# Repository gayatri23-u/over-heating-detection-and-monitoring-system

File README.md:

# Over Heating Detection and Monitoring System

## Overview
This project is a PCB-based Over Heating Detection and Monitoring System developed to monitor temperature levels and detect overheating conditions in electronic systems.

The system continuously reads temperature data from sensors and provides alerts when the temperature exceeds a predefined threshold.

## Features
- Real-time temperature monitoring
- Overheating detection
- Alert/notification mechanism
- Custom PCB design
- Arduino-based implementation
- Compact and efficient system

## Technologies Used
- Arduino
- Embedded C/C++
- PCB Design
- Temperature Sensors

## Files Included
- Arduino source code
- PCB board design (.brd)
- Schematic files (.sch)

## Applications
- Industrial safety systems
- Electronic device monitoring
- Automation projects
- Temperature protection systems

## Author
Gayatri Pawar

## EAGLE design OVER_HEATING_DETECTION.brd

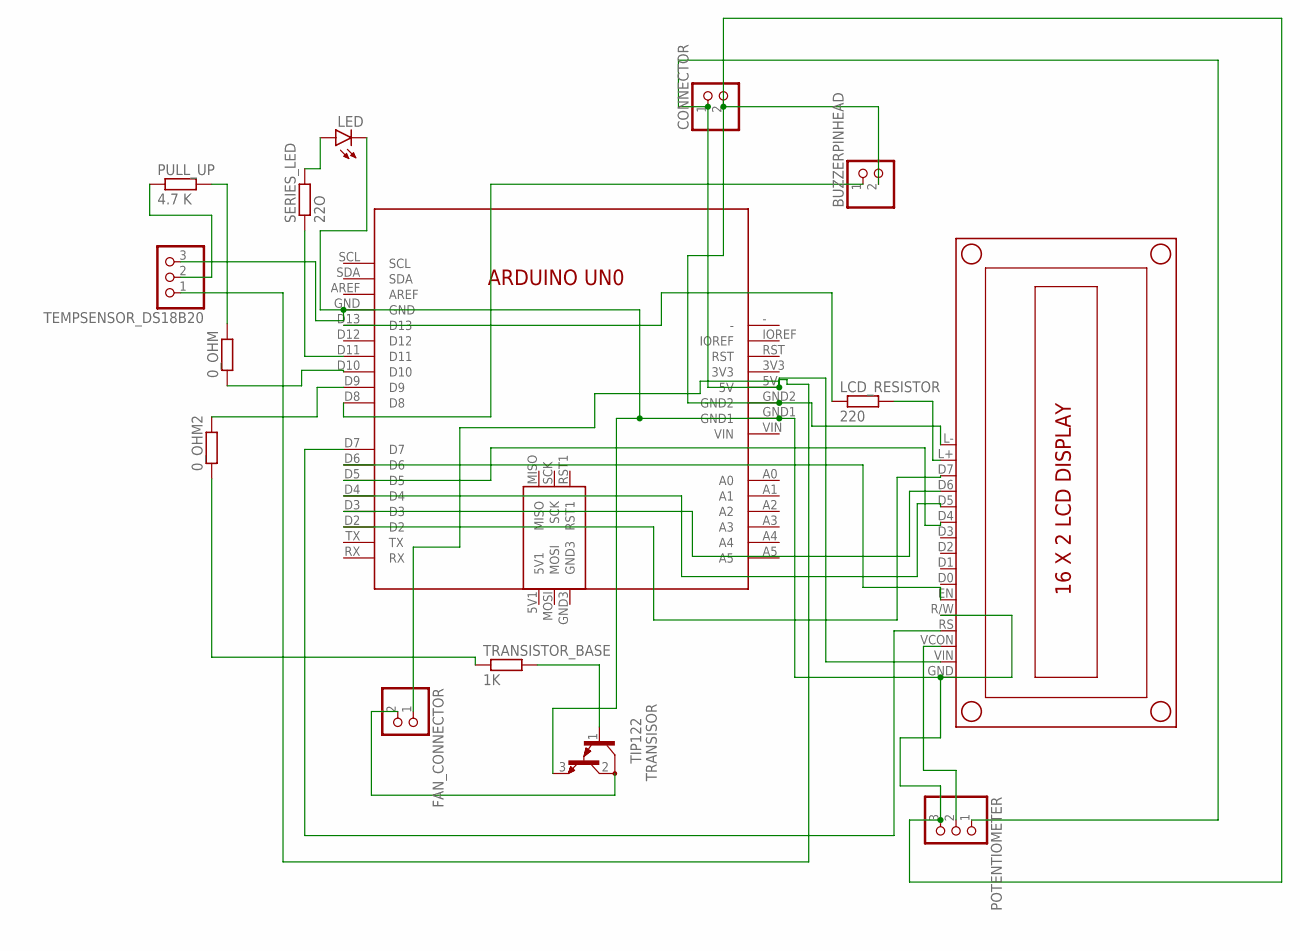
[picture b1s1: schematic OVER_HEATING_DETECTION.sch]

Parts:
0_OHM, 0_OHM2: R-EU_0204/7; 0204/7
BUZZERPINHEAD: PINHD-1X2; 1X02
CONNECTOR: PINHD-1X2; 1X02
FAN_CONNECTOR: PINHD-1X2; 1X02
LCD_RESISTOR: 220; 0204/7
LED: LED5MM
POTENTIOMETER: PINHD-1X3; 1X03
PULL_UP: 4.7 K; 0204/7
SERIES_LED: 22O; 0204/7
TEMPSENSOR_DS18B20: PINHD-1X3; 1X03
TRANSISOR: TIP122; TO220
TRANSISTOR_BASE: 1K; 0204/7
U$1: ARDUINO_UNO
U$2: 16X2_LCD_DISPLAY

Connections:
unnamed: U$1.D2, U$2.D7
unnamed: U$1.D3, U$2.D6
unnamed: U$1.D4, U$2.D5
unnamed: U$1.D5, U$2.D4
unnamed: U$1.D6, U$2.EN
unnamed: U$1.D7, U$2.RS
unnamed: BUZZERPINHEAD.1, U$1.D8
unnamed: 0_OHM2.1, TRANSISTOR_BASE.1
unnamed: TRANSISOR.1 (B), TRANSISTOR_BASE.2
unnamed: 0_OHM.1, U$1.D10
unnamed: PULL_UP.1, TEMPSENSOR_DS18B20.2
unnamed: LED.A, SERIES_LED.2
unnamed: SERIES_LED.1, U$1.D11
unnamed: BUZZERPINHEAD.2, CONNECTOR.2, LED.K (C), POTENTIOMETER.3, TEMPSENSOR_DS18B20.3, TRANSISOR.3 (E), U$1.GND, U$1.GND1, U$1.GND2, U$2.GND, U$2.L-, U$2.R/W
unnamed: LCD_RESISTOR.1, U$1.D13
unnamed: LCD_RESISTOR.2, U$2.L+
unnamed: 0_OHM.2, PULL_UP.2
unnamed: CONNECTOR.1, FAN_CONNECTOR.1, POTENTIOMETER.1, TEMPSENSOR_DS18B20.1, U$1.5V, U$2.VIN
unnamed: POTENTIOMETER.2, U$2.VCON
unnamed: 0_OHM2.2, U$1.D9
unnamed: FAN_CONNECTOR.2, TRANSISOR.2 (C)

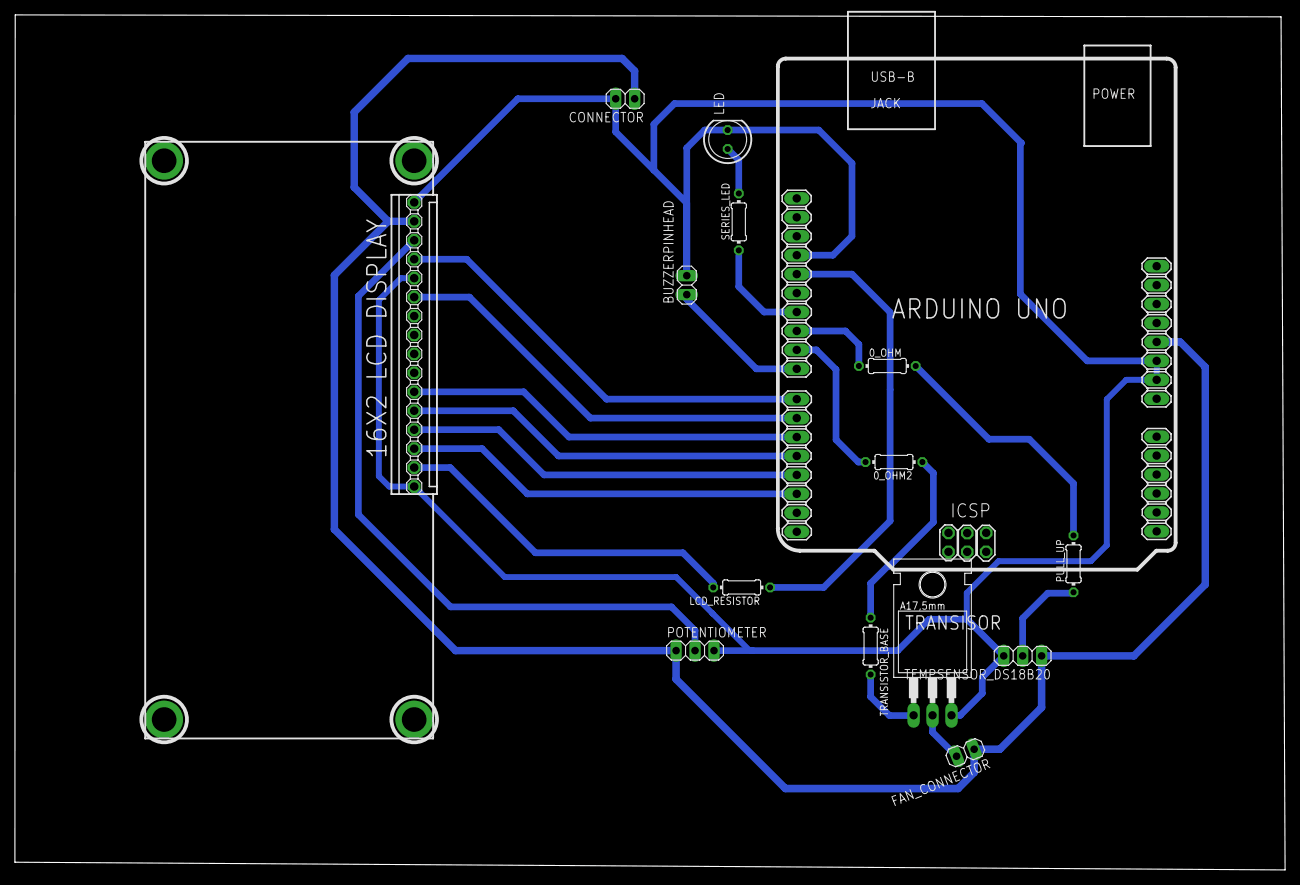
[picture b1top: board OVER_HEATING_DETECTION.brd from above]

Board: 2 copper layers, 170.3 x 114.7 mm, 15 parts (0 on the bottom side), 21 nets.

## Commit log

2026-05-11 Add files via upload
    Initial project upload
2026-05-11 Add files via upload
    Implemented temperature monitoring logic, sensor handling, and overheating alert functionality using Arduino.
